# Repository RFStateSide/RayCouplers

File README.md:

# RayCouplers

RayCouplers is RF StateSide LLC's directional-coupler project for forward and
reflected RF detection, power measurement, SWR monitoring and protection-system
experiments.

**Public Engineering Reference — AS-IS.** The editable designs, population BOMs,
manufacturing files and historical measurements support study, independent
construction, modification and continued development.

## Overview

The project was developed for RF measurement and protection applications using
RayPowerMeter and RayRailSwSense. It provides 200 W and 2 kW population
configurations on one common PCB. These names identify configurations; they do
not establish guaranteed continuous-power capability or measurement accuracy.

The original hardware was fabricated, manually populated with SMT reflow and
tested during RF StateSide development. The supplied common PCB incorporates
curated source and documentation. Its SOD-123 manufacturing revision has not
itself been physically fabricated and validated.

## Features and Design

The circuits provide forward/reflected detector signals, an interrupt-selection
circuit and a cascaded frequency divider documented as divide by four. J4 carries
+3.3 V, FWD, REF, INT and GND. Transformer construction and resistor populations
differ between configurations.

See [configuration details](docs/variant-configurations.md) for component values,
interface assignments and the historical jumper settings.

## Hardware Configurations

| Item | 200 W | 2 kW |
|---|---|---|
| D1/D2 | BAT42W | BAT42W |
| R7/R11 | 3.3 kΩ | 3.9 kΩ |
| R8/R12 | 1.6 kΩ | 1.2 kΩ |
| R23 | 2.7 kΩ | 2.7 kΩ |
| C1/C2 | 10 nF | 10 nF |
| Turns per T1/T2 | 16 | 24 |
| Fair-Rite #43 cores per transformer | One | Two taped together |

Both configurations use Fair-Rite 5943001401 cores and 21 AWG high-temperature
enameled copper wire. Use the matching [population BOM](bom/README.md); the PCB's
default component values describe the 200 W configuration.

## Common PCB Design

The two-layer board measures 70 mm × 102 mm. It includes two routed internal
openings, four grounded 3.2 mm mounting holes and SOD-123 detector lands.

Open [the common KiCad project](hardware/common/RayCouplers.kicad_pro) for the PCB
and 200 W schematic. Open [the 2 kW project](hardware/variants/2kw/RayCouplers.kicad_pro)
for its population schematic. There is one authoritative editable PCB, not a
separate routed board for each population.

KiCad 9 and its stock libraries are required. Project-local custom libraries are
included; see [library information](hardware/libraries/README.md). For source
changes and derived projects, follow [the editing workflow](docs/editing-workflow.md).

## Transformer Construction

The 200 W configuration uses one toroid for each transformer; the 2 kW
configuration uses two taped toroids for each transformer. The [construction
guide](docs/transformer-construction.md) records materials, winding method,
schematic connections and an experimental photograph.

Physical lead mapping, winding orientation and insulation details are incomplete
in the historical records. Verify them before reproducing an assembly.

## Manufacturing and Assembly

The [P3-prep-01 manufacturing package](manufacturing/README.md) supplies one
Gerber/drill set for both configurations. Read [fabrication requirements](docs/fabrication.md)
and [package verification](docs/distribution-integrity.md) before manufacture.
The retained approximately 0.2 mm clearance requires fabricator CAM acceptance;
it is not strict 8-mil spacing compliance.

Follow [common assembly](docs/assembly/common.md), then the
[200 W](docs/assembly/200w.md) or [2 kW](docs/assembly/2kw.md) instructions.
Historical January 2026 fabrication used SOD-323 detector pads and is distinct
from the supplied SOD-123 package.

## Calibration and Testing

Historical forward measurements contain 19 points through 250 W for the 200 W
configuration and 14 points through 1500 W for the 2 kW configuration. Each new
system requires its own calibration.

[Calibration traceability](calibration/profile-traceability.md) distinguishes
measured data from estimated endpoints and experimental reflected adjustments.
The [engineering audit](PUBLIC_RELEASE_AUDIT.md) records automated CAD checks,
manufacturing integrity and separately reported Linux inspection. These checks
do not establish physical RF performance of the supplied revision.

## Repository Contents

| Location | Contents |
|---|---|
| [hardware/](hardware/) | Common PCB, population schematics and local libraries |
| [bom/](bom/) | Population and procurement reference CSVs |
| [calibration/](calibration/) | Measured excerpts and calibration traceability |
| [manufacturing/](manufacturing/) | Controlled common-PCB fabrication package |
| [docs/](docs/) | Construction, history, sourcing, limitations and licensing |
| [tools/](tools/) | Python generation and verification utilities |
| [PUBLIC_RELEASE_AUDIT.md](PUBLIC_RELEASE_AUDIT.md) | Attributed technical validation record |

Original measurement workbooks and supplier archives are retained privately.
They are not required to open the supplied designs or check the package.

## Development Tools

KiCad was used for schematic capture and PCB design. Python utilities support
source verification and manufacturing-package integrity checks. Git and GitHub
provide version control and access to the engineering source.

ChatGPT by OpenAI and OpenAI Codex assisted with engineering review,
documentation, source organization, validation and preparation of the
open-hardware reference. RF StateSide LLC performed the original hardware
design, assembly and historical RF testing.

## Known Limitations

The supplied SOD-123 revision has not received physical fabrication acceptance.
Calibration, connector fit, transformer construction and operating suitability
require verification for each implementation. Frequency coverage, temperature
dependence and complete measurement conditions are not established by the
available records. No commercial certification or guaranteed performance is
claimed. Read [known limitations](docs/known-limitations.md).

## License

Copyright RF StateSide LLC. Original project contributions are provided under
**CERN-OHL-P v2.0**, SPDX **CERN-OHL-P-2.0**. The official [LICENSE](LICENSE) is
authoritative; retain [NOTICE](NOTICE) and applicable third-party notices.

See [licensing](docs/licensing.md) and [asset provenance](docs/asset-provenance.md)
for scope and separately licensed material.

## Credits and Acknowledgments

RF StateSide LLC developed the original hardware and contributed the custom CAD
work. KiCad library contributors supplied the upstream elements identified in the
library notices. Manufacturer documentation supports component identification;
candidate parts are distinguished from historically installed parts.

Canonical repository: [RFStateSide/RayCouplers](https://github.com/RFStateSide/RayCouplers).

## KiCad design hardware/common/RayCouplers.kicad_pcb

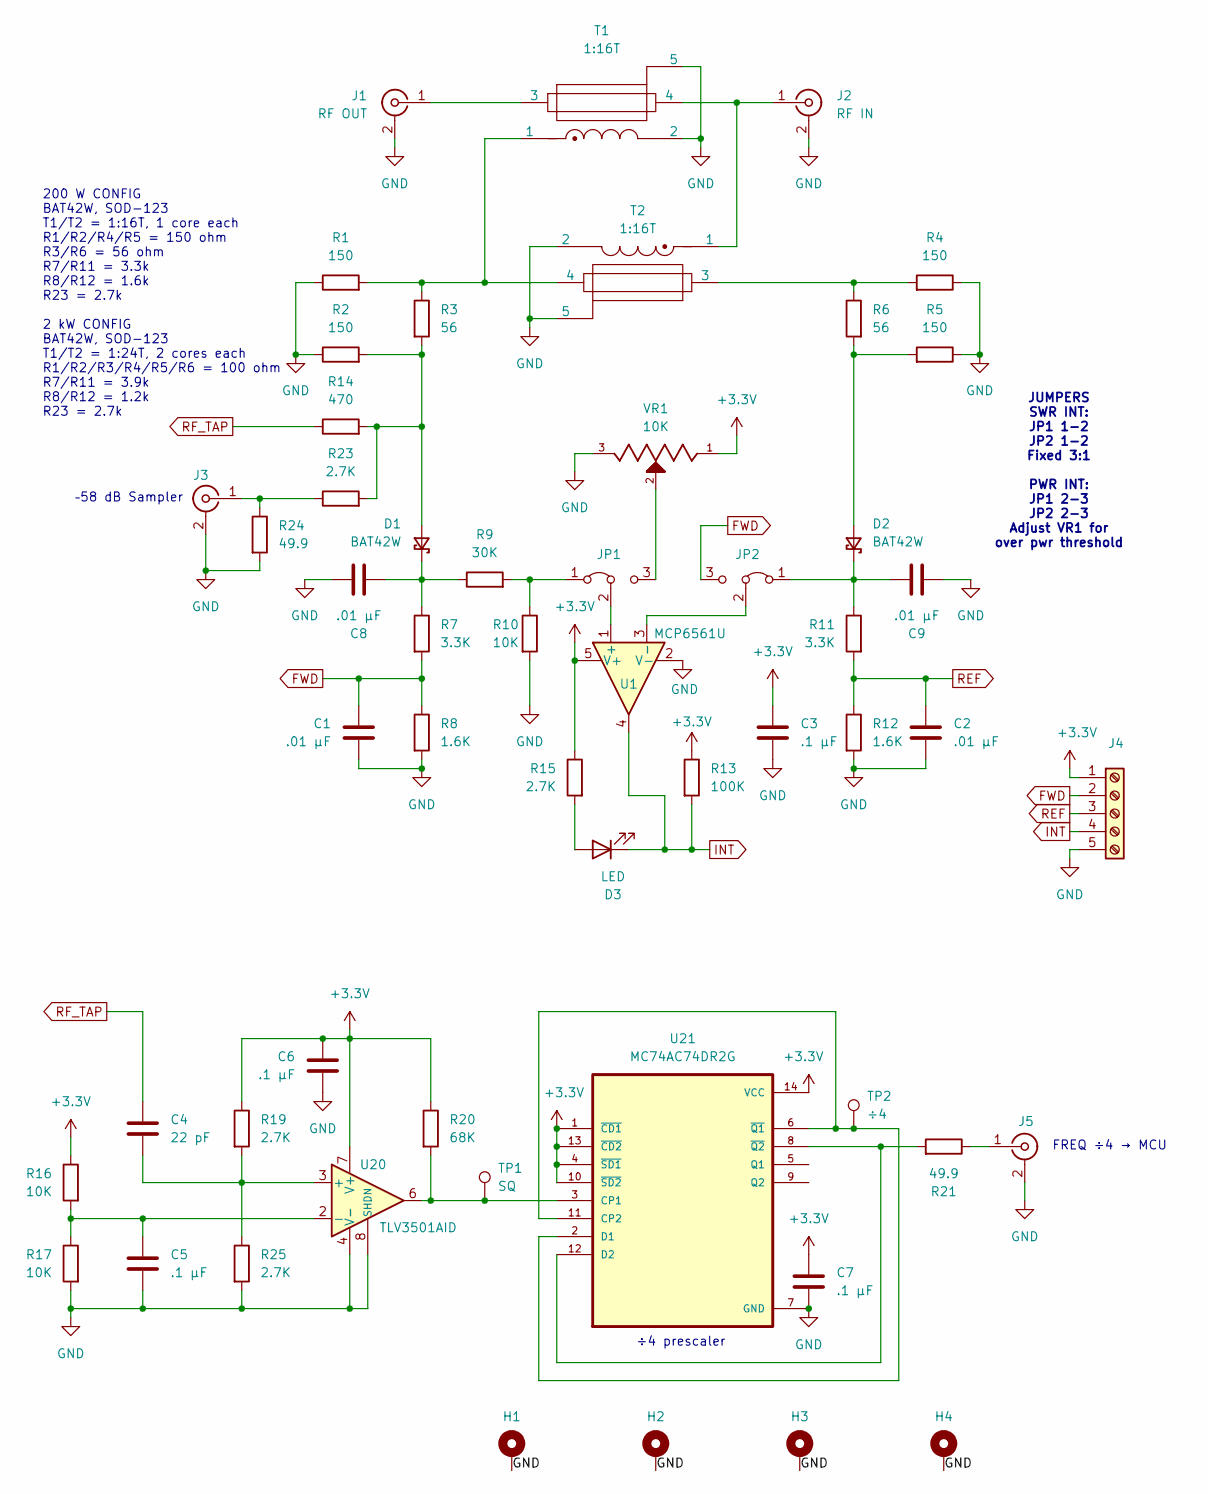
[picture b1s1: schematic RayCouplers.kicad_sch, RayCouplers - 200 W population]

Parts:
C1, C2, C8, C9: .01 µF; C_0805_2012Metric_Pad1.18x1.45mm_HandSolder; MPN CL21B103KDCNNNC
C3, C5, C6, C7: .1 µF; C_0805_2012Metric_Pad1.18x1.45mm_HandSolder; MPN CL21B104KBCNFNC
C4: 22 pF; C_0805_2012Metric_Pad1.18x1.45mm_HandSolder; MPN CL21C220JBANFNC
D1, D2: BAT42W; D_SOD-123_handSoldering; MPN BAT42W_R1_00001
D3: LED; LED_0805_2012Metric_Pad1.15x1.40mm_HandSolder; MPN LSM0805412V
H1, H2, H3, H4: MountingHole_Pad; MountingHole_3.2mm_M3_ISO7380_Pad_TopBottom_Gnd
J1: RF OUT; RF_Pad_HF; MPN 83-1R
J2: RF IN; RF_Pad_HF; MPN 83-1R
J3: Conn_Coaxial; RF_Pad_HF_Sm; MPN RF1-106-D-00-50-HDW
J4: Screw_Terminal_01x05; TerminalBlock_Phoenix_MPT-0,5-5-2.54_1x05_P2.54mm_Horizontal
J5: Conn_Coaxial; RF_Pad_HF_Sm
JP1, JP2: Jumper_3_Bridged12; PinHeader_1x03_P2.54mm_Vertical
R1, R2, R4, R5: 150; R_2512_6332Metric_Pad1.40x3.35mm_HandSolder; MPN RMCF2512FT150R
R3, R6: 56; R_2512_6332Metric_Pad1.40x3.35mm_HandSolder; MPN RMCF2512FT56R0
R7, R11: 3.3K; R_0805_2012Metric_Pad1.20x1.40mm_HandSolder; MPN RMCF0805FT3K30
R8, R12: 1.6K; R_0805_2012Metric_Pad1.20x1.40mm_HandSolder; MPN RMCF0805FT1K60
R9: 30K; R_0805_2012Metric_Pad1.20x1.40mm_HandSolder; MPN RMCF0805FT30K0
R10, R16, R17: 10K; R_0805_2012Metric_Pad1.20x1.40mm_HandSolder; MPN RMCF0805FT10K0
R13: 100K; R_0805_2012Metric_Pad1.20x1.40mm_HandSolder; MPN RMCF0805FT100K
R14: 470; R_0805_2012Metric_Pad1.20x1.40mm_HandSolder; MPN RMCF0805FT470R
R15, R19, R23, R25: 2.7K; R_0805_2012Metric_Pad1.20x1.40mm_HandSolder; MPN RMCF0805FT2K70
R20: 68K; R_0805_2012Metric_Pad1.20x1.40mm_HandSolder; MPN RMCF0805FT1M00
R21, R24: 49.9; R_0805_2012Metric_Pad1.20x1.40mm_HandSolder; MPN RMCF0805FT47R0
T1, T2: 1:16T; SWRVoltageTransformer
TP1: SQ; TestPoint_Pad_2.5x2.5mm
TP2: ÷4; TestPoint_Pad_2.5x2.5mm
U1: MCP6561U; SOT-23-5_HandSoldering; MPN MCP6561UT-E/OT
U20: TLV3501AID; SOIC-8_3.9x4.9mm_P1.27mm; MPN TLV3501AID
U21: MC74AC74DR2G; SOIC127P600X175-14N; MPN MC74AC74DR2G
VR1: 10K; TRIM_3296W1103LF; PARTREV 05/16

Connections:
+3.3V: C3.1, C6.1, C7.1, J4.1, R13.1, R15.1, R16.1, R19.1, R20.1, U1.5 (V+), U20.7 (V+), U21.1 (~CD1), U21.4 (~SD1), U21.10 (~SD2), U21.13 (~CD2), U21.14 (VCC), VR1.1
FWD: C1.1, J4.2, JP2.3 (B), R7.2, R8.1
GND: C1.2, C2.2, C3.2, C5.2, C6.2, C7.2, C8.2, C9.1, H1.1, H2.1, H3.1, H4.1, J1.2 (Ext), J2.2 (Ext), J3.2 (Ext), J4.5, J5.2 (Ext), R1.1, R2.1, R4.1, R5.1, R8.2, R10.2, R12.2, R17.2, R24.2, R25.2, T1.2, T1.5, T2.2, T2.5, U1.2 (V-), U20.4 (V-), U20.8 (SHDN), U21.7 (GND), VR1.3
INT: D3.1 (K), J4.4, R13.2, U1.4
unnamed: D1.2 (A), R2.2, R3.2, R14.2, R23.2
unnamed: C8.1, D1.1 (K), R7.1, R9.1
unnamed: D2.2 (A), R5.2, R6.2
unnamed: C9.2, D2.1 (K), JP2.1 (A), R11.1
unnamed: D3.2 (A), R15.2
unnamed: J1.1 (In), T1.3
unnamed: J2.1 (In), T1.4, T2.1
unnamed: J3.1 (In), R23.1, R24.1
unnamed: J5.1 (In), R21.1
unnamed: JP1.1 (A), R9.2, R10.1
unnamed: JP1.3 (B), VR1.2
unnamed: JP1.2 (C), U1.1 (+)
unnamed: JP2.2 (C), U1.3 (-)
unnamed: R1.2, R3.1, T1.1, T2.4
unnamed: R4.2, R6.1, T2.3
unnamed: C4.2, R19.2, R25.1, U20.3 (+)
unnamed: C5.1, R16.2, R17.1, U20.2 (-)
unnamed: R20.2, TP1.1, U20.6, U21.3 (CP1)
unnamed: TP2.1, U21.2 (D1), U21.6 (~Q1), U21.11 (CP2)
unnamed: R21.2, U21.8 (~Q2), U21.12 (D2)
REF: C2.1, J4.3, R11.2, R12.1
RF_TAP: C4.1, R14.1

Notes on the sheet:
–58 dB Sampler
JUMPERS SWR INT: JP1 1-2 JP2 1-2 Fixed 3:1 PWR INT: JP1 2-3 JP2 2-3 Adjust VR1 for over pwr threshold
÷4 prescaler
FREQ ÷4 → MCU
200 W CONFIG BAT42W, SOD-123 T1/T2 = 1:16T, 1 core each R1/R2/R4/R5 = 150 ohm R3/R6 = 56 ohm R7/R11 = 3.3k R8/R12 = 1.6k R23 = 2.7k 2 kW CONFIG BAT42W, SOD-123 T1/T2 = 1:24T, 2 cores each R1/R2/R3/R4/R5/R6 = 100 ohm R7/R11 = 3.9k R8/R12 = 1.2k R23 = 2.7k

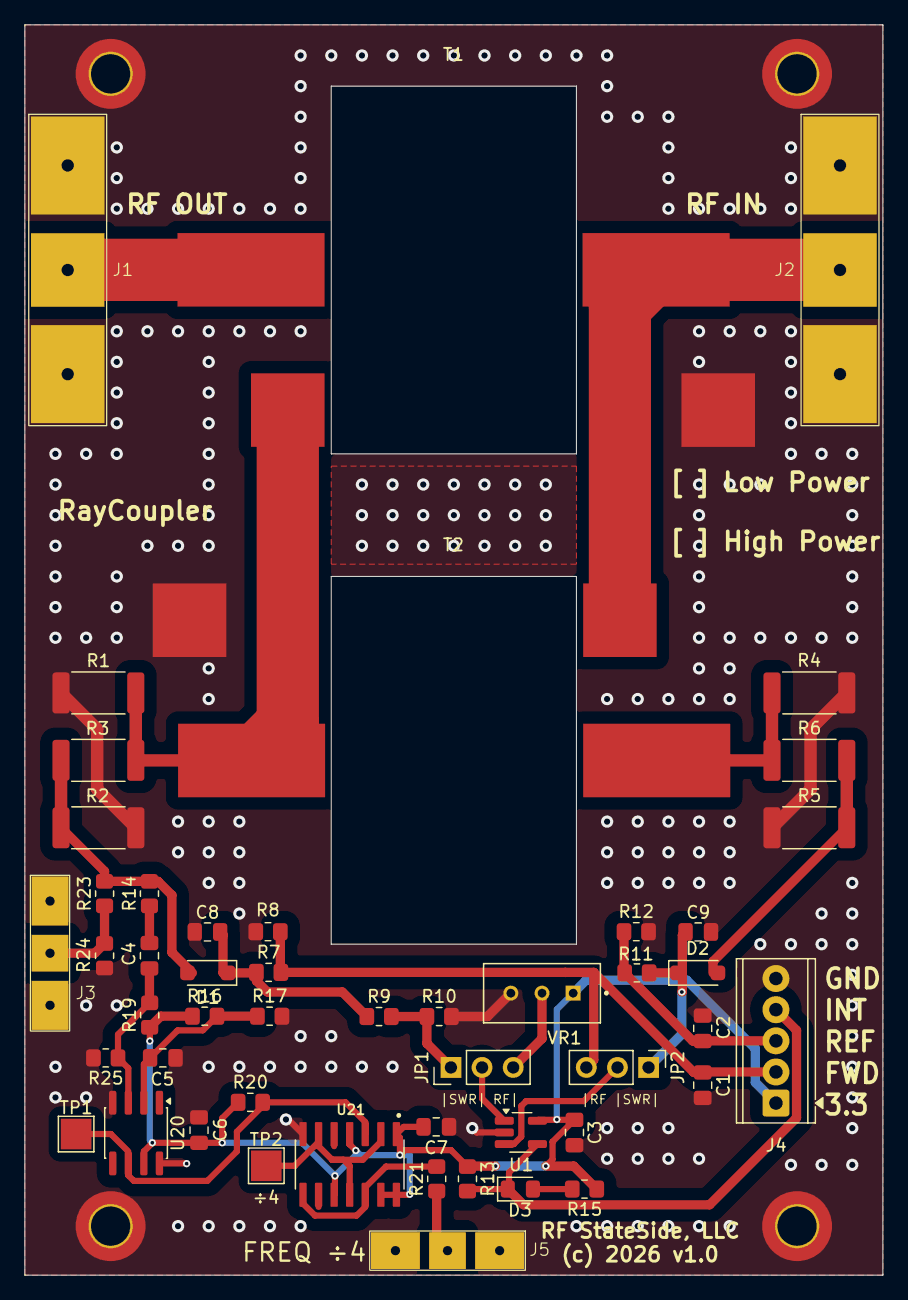
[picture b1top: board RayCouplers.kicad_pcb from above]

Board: 2 copper layers, 70.0 x 102.0 mm, 54 parts (0 on the bottom side), 26 nets.

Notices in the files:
hardware/common/RayCouplers.kicad_pcb:
CERN-OHL-P-2.0; see NOTICE and LICENSE
(c) 2026 v1.0
hardware/common/RayCouplers.kicad_sch:
Copyright RF StateSide LLC | CERN-OHL-P-2.0; see NOTICE and LICENSE
